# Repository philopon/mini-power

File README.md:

# mini-power

mini power manager for PC

## PCB

### KiCad dependencies

- [TLP172AM](https://www.digikey.jp/ja/models/6679819)
- [SparkFun-Connector](https://github.com/sparkfun/SparkFun-KiCad-Libraries/blob/main/Symbols/SparkFun-Connector.kicad_sym)
- [Seeed Series Kicad files](https://wiki.seeedstudio.com/SeeedStudio_XIAO_Series_Introduction/#seeed-series-kicad-files)

### BOM

- U1: [Seeed Studio XIAO ESP32C6](https://akizukidenshi.com/catalog/g/g129481/) x 1
- U2-U4: [TLP172AM](https://akizukidenshi.com/catalog/g/g116065/) x 3
- J1: [1x5 pin socket](https://akizukidenshi.com/catalog/g/g110397/) x 2
- 1206 SMD resistor
  - R1,R3: 200R x 2
  - R2: 330R x 1
- [PCB](gerber.zip) x 1

## write firmware

```
$ cp src/config.cpp.template src/config.cpp
# Edit src/config.cpp

# install npm packages
$ cd frontend
$ pnpm install

# build and send firmware using platformio

```

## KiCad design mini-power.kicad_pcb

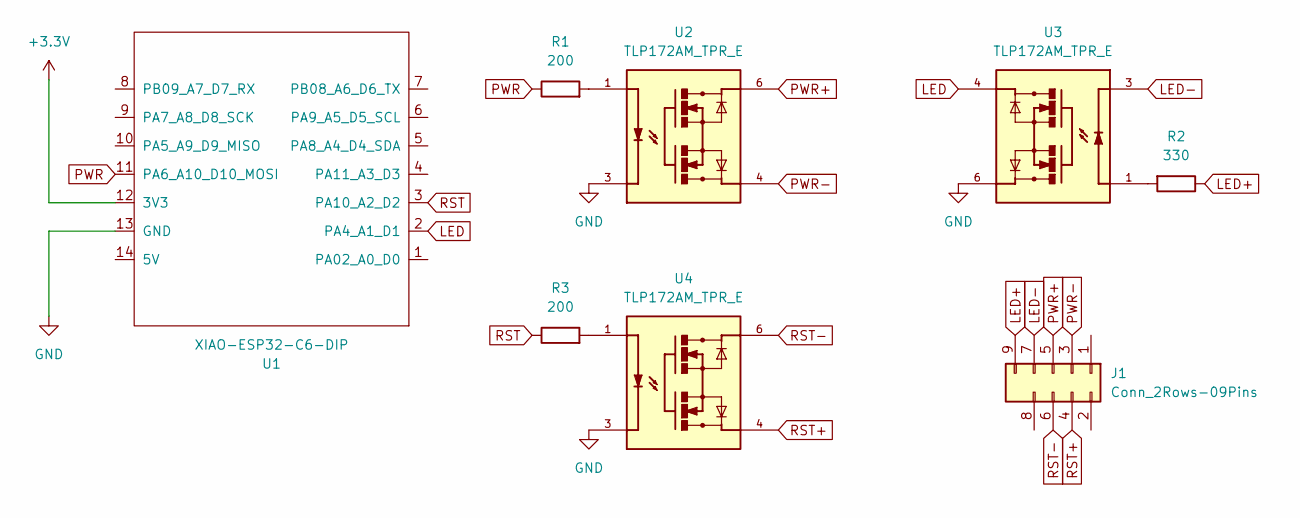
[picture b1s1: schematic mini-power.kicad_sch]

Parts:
J1: Conn_2Rows-09Pins; PinHeader_2x05_P2.54mm_Vertical
R1, R3: 200; R_1206_3216Metric
R2: 330; R_1206_3216Metric
U1: XIAO-ESP32-C6-DIP; XIAO-ESP32C6-DIP
U2, U3, U4: TLP172AM_TPR_E; SOIC254P700X220-4N; PARTREV 5.0

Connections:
+3.3V: U1.12 (3V3)
GND: U1.13 (GND), U2.3, U3.6, U4.3
LED: U1.2 (PA4_A1_D1), U3.4
LED+: J1.9, R2.1
LED-: J1.7, U3.3
unnamed: R1.2, U2.1
unnamed: R2.2, U3.1
unnamed: R3.2, U4.1
PWR: R1.1, U1.11 (PA6_A10_D10_MOSI)
PWR+: J1.5, U2.6
PWR-: J1.3, U2.4
RST: R3.1, U1.3 (PA10_A2_D2)
RST+: J1.4, U4.4
RST-: J1.6, U4.6

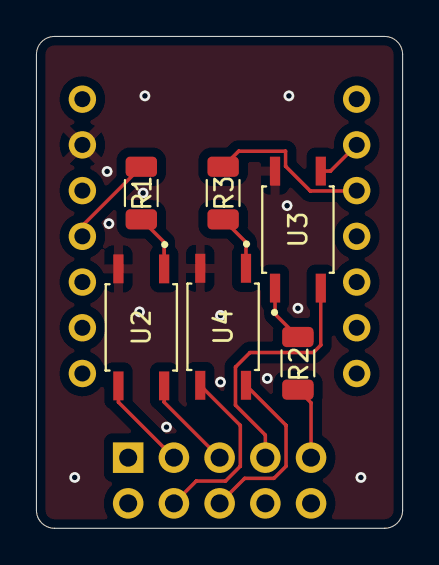
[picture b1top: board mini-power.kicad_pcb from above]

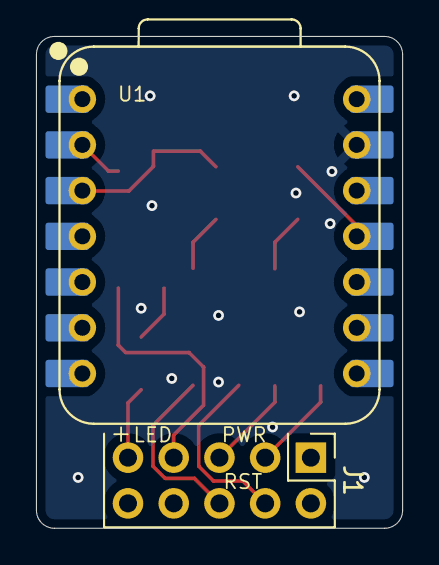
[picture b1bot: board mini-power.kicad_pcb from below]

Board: 2 copper layers, 20.3 x 27.3 mm, 8 parts (2 on the bottom side), 13 nets.

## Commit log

2025-01-17 add KiCAD files
2025-01-17 add firmware files
2025-01-17 add images to README.md
2025-01-17 align images
2025-01-18 add logging
2025-01-18 add config.cpp template
2025-01-18 fix build.py for frontend
2025-01-18 remove svelteesp32.h
2025-01-18 add #pragma once line
2025-01-18 change directory structure
2025-01-18 use pnpm instead of npm
